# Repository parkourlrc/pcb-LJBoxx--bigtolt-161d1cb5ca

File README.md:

# BigTOLT - Big(kinda) esc with TOLT mosfets

18 mosfet TOLT package esc design based off vesc6 schematic and compatible with [VESC](https://github.com/vedderb/bldc) firmware.

There is also a small high voltage converter used for higher voltage operation, aim was to have a quite big voltage operation range. But if you will test it with high voltage, please do mind that the voltage sensing is **un-isolated**

# Tested !!
This board is tested but the pcb needs some fixes (will do soon). BOM and gerber are in [here](/tolt)

## Board preview

## Liability
This project sources are provided **as is** therfore I, and the co controbutors to this repository shall not be held responsible for any damage occured, including but not limited to hardware damages or other physical injury caused by the outcomes of this source. **You are responsible for your actions. If used wrong, it will go wrong!**

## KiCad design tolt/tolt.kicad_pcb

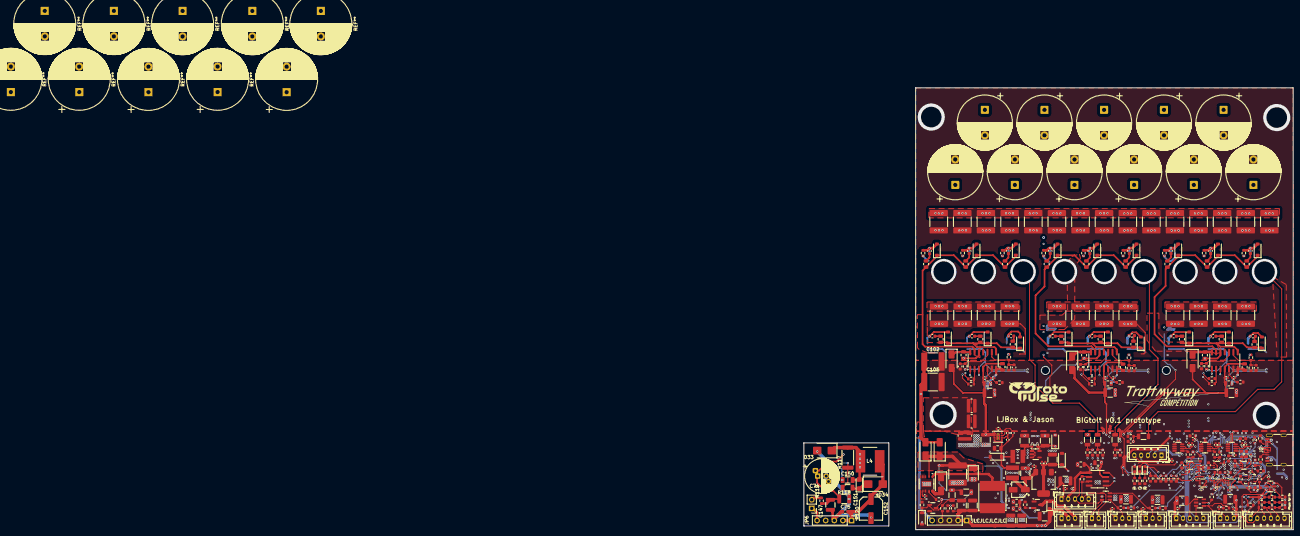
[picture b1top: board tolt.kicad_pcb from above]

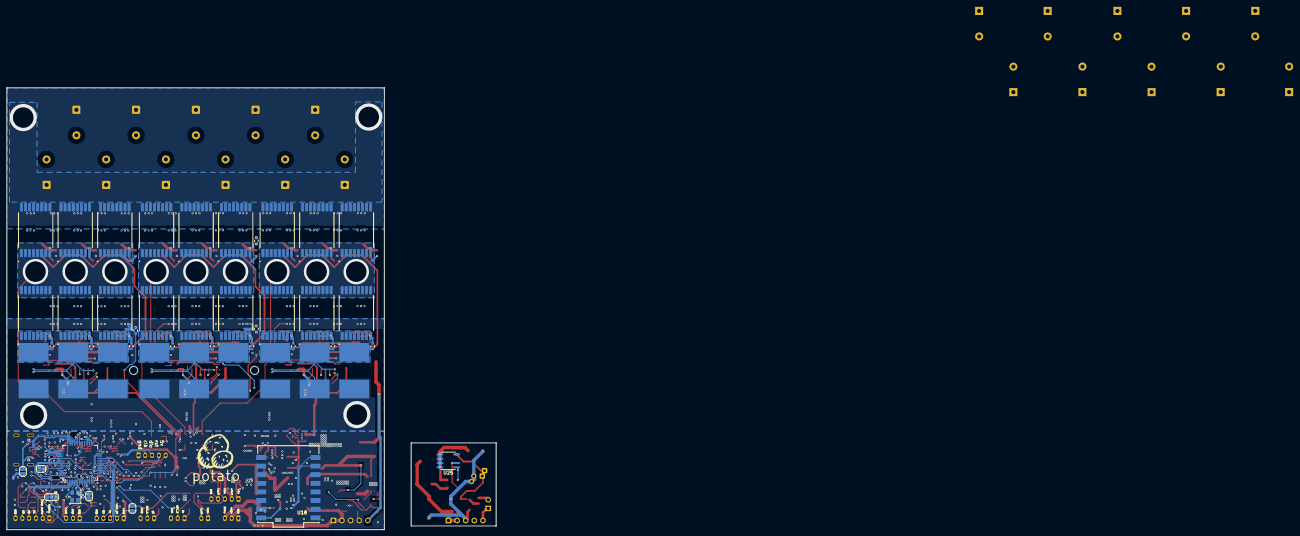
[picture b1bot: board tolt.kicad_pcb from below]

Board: 6 copper layers, 111.1 x 130.0 mm, 398 parts (50 on the bottom side), 164 nets.

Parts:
C1, C2, C3, C4, C24, C25, C26, C27, C28, C31, C32, C33, C34, C37, C38, C39, C45, C46, C47, C48, C49, C50, C76, C79, C80, C82, C87, C144: 100n; C_0402_1005Metric
C5, C6, C7, C8, C9, C10, C13, C14, C58, C59, C60, C78: 2.2uf; C_0603_1608Metric
C11, C12: 15p; C_0402_1005Metric
C15, C17, C19, C21, C22, C23, C81, C83, C84, C91, C111, C145, C146: 4.7u; C_0805_2012Metric
C16, C18, C20: 220nF; C_0402_1005Metric
C29, C36, C41: 15n; C_0603_1608Metric
C30, C35, C40, C51, C52, C53, C153, C154, C155: 1n; C_0603_1608Metric
C42, C43, C44, C71, C85, C88, C149: 10uF; C_1210_3225Metric
C54, C55, C56, C57: 100n; C_0603_1608Metric
C61: 33uF; CP_Elec_4x5.4
C62, C64, C67, C69, C116, C118, C120, C122, C123, C125, C127: 100nF; C_0402_1005Metric
C63, C65, C68, C70, C117, C119, C121, C124, C126: 2.2uF; C_1210_3225Metric
C66: 100uF; C_0402_1005Metric
C72: 430pF; R_0402_1005Metric
C73: 47uF; C_0805_2012Metric
C74: 33uF; CP_Radial_D10.0mm_P2.50mm_P5.00mm
C75: 470nF; C_1210_3225Metric
C77, C148: 22uF; C_1210_3225Metric
C86: 33uF; CP_EIA-3528-15_AVX-H
C89, C90, C92, C93, C94, C95, C96, C97, C98, C99, C100: 560u; CP_Radial_D16.0mm_P7.50mm
C101, C102, C103, C104, C105, C106, C107, C108, C109, C110, C112, C113, C114, C115, C128, C129, C130, C131, C132, C133, C134, C135, C136, C137, C138, C139, C140, C141, C142, C143: 1uf; C_2220_5750Metric
C147: 100n; C_1210_3225Metric
C150: 100nF; C_1206_3216Metric
C151: 10uF; CP_EIA-3216-18_Kemet-A
C152: 100uF; CP_Elec_6.3x5.4
D1, D2, D3: STTH2R06A; D_SMA
D4, D5, D6, D7, D8, D9, D10, D11, D12, D13, D14, D15, D16, D17, D18, D19, D20, D21: D; D_SOD-123
D22: green; LED_0603_1608Metric
D23: MMSZ5242B; D_SOD-123
D24, D25: BZT52C3V6-7-F; D_SOD-123
D26: red; LED_0603_1608Metric
D27: blue; LED_0603_1608Metric
D28: BAT46W; D_SOD-323F
D29: BZT52C5V6-7-F; D_SOD-123
D30, D31, D32: SS1200; D_SMA
D33, D34: STTH1R06U; D_SMB
FB1, FB2, FB3, FB4, FB5, FB6, FB7, FB8, FB9, FB10, FB11, FB12, FB13, FB14, FB15, FB16, FB17, FB18: FerriteBead; C_0603_1608Metric
J1, J4, J7: Conn_01x05; JST_PH_B5B-PH-K_1x05_P2.00mm_Vertical
J2: USB_C_Receptacle_USB2.0; USB_C_Receptacle_G-Switch_GT-USB-7010ASV
J3: Conn_01x06; JST_PH_B6B-PH-K_1x06_P2.00mm_Vertical
J5, J6, J9, J10: Conn_01x03; JST_PH_B3B-PH-K_1x03_P2.00mm_Vertical
J8: Conn_01x02; JST_PH_B2B-PH-K_1x02_P2.00mm_Vertical
J11, J11#2: Conn_01x05; PinHeader_1x05_P2.54mm_Vertical
J14: BOOT0; SolderJumper-2_P1.3mm_Open_RoundedPad1.0x1.5mm
J15: NRST; SolderJumper-2_P1.3mm_Open_RoundedPad1.0x1.5mm
JP1: Jumper_3_Bridged12; SolderJumper-3_P1.3mm_Bridged2Bar12_RoundedPad1.0x1.5mm
JP2, JP3: Jumper_2_Open; SolderJumper-2_P1.3mm_Open_RoundedPad1.0x1.5mm
JP6: Jumper_2_Open; PinHeader_1x02_P2.54mm_Vertical
L1, L2: 10uh; IND-SMD_L3.9-W3.9-1
L4: 1.5mH; L_Bourns_SRN8040TA
L5: 220uH; IND-SMD_L8.0-W8.0_FNR80XXS
Q1, Q2, Q3, Q4, Q5, Q6, Q7, Q8, Q9, Q10, Q11, Q12, Q13, Q14, Q15, Q16, Q17, Q18: NMOS; HDSOP-16-2
Q19: CJ3400; SOT-23
Q20: BSS131; SOT-23
R1, R2, R3, R37, R38, R39, R40, R41, R42, R52, R54, R55, R56, R57, R61, R62, R63, R72, R85, R86, R87, R88, R89, R90, R91, R92, R93, R99, R103, R104, R105, R106, R107, R108, R109, R110, R111, R121: 10k; R_0603_1608Metric
R4, R68, R69: 0; R_0815_2038Metric
R5, R6, R7, R8, R9, R10, R14, R15, R16, R17, R18, R19, R23, R24, R25, R27, R28, R29: 24r; R_0805_2012Metric
R11, R12, R13, R20, R21, R22, R30, R31, R32: 0.3mr; R5930
R26, R84: 5k1; R_0603_1608Metric
R33, R34, R35, R67, R70, R71, R115: 1k; R_0603_1608Metric
R36, R51, R53: 320k; R_0603_1608Metric
R43, R45, R47: 240k; R_1206_3216Metric
R44, R46, R48: 5.1k; R_0603_1608Metric
R49, R96: 470k; R_1206_3216Metric
R50: 10.2k; R_0603_1608Metric
R58, R59, R60: 10k_NTC; R_0603_1608Metric_Pad0.98x0.95mm_HandSolder
R64: 523k; R_0402_1005Metric
R65, R66: 220r; R_0603_1608Metric
R73, R74, R75, R79, R81, R100, R101, R102: 2k2; R_0603_1608Metric
R76, R77, R78, R80, R82: 4.3k; R_0603_1608Metric
R83: 120ohm; R_0603_1608Metric
R94, R95: 100k; R_0402_1005Metric
R97: 470r; R_0603_1608Metric
R98, R122, R123, R124: 100r; R_0603_1608Metric
R112: 2.8M; R_0603_1608Metric
R113: 200k; R_0603_1608Metric
R114: 4.7M; R_1206_3216Metric
R116: 100k; R_0603_1608Metric
R117: 2k; R_2512_6332Metric
R118: 12.7k; R_1206_3216Metric
R119: 0; R_0603_1608Metric
R120: 4k; R_0603_1608Metric
U1: STM32F405RGTx; LQFP-64_10x10mm_P0.5mm
U2, U3, U4: L6491; SO-14_3.9x8.65mm_P1.27mm
U5, U7, U9: INA240/241; SOT-23-8
U6, U8, U10, U11, U12, U13: MC74VHC1GT66; SOT-353_SC-70-5
U14: AMS1117-3.3; SOT-223-3_TabPin2
U15: LP5907MFX-3.3; SOT-23-5
U16: TPS82130; Texas_SIL0008D_MicroSiP-8-1EP_2.8x3mm_P0.65mm_EP1.1x1.9mm_T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
U17: BMI323; Bosch_LGA-14_3x2.5mm_P0.5mm
U18: ESP32-C3_SUPERMINI_SMD; MODULE_ESP32-C3_SUPERMINI
U20: TJA1051T-3; SOIC-8_3.9x4.9mm_P1.27mm
U21, U22, U23: SRV05-4; SOT-23-6
U24: LTC7138xMSE; Analog_MSOP-12-16-1EP_3x4.039mm_P0.5mm_EP1.651x2.845mm
U25: LNK306D; PowerIntegrations_SO-8C
Y1: 8m; Crystal_SMD_3225-4Pin_3.2x2.5mm

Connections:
+5V: C73.2, C80.2, C83.2, C84.2, C91.2, C118.1, C119.1, C120.1, C121.1, C122.2, C125.1, C126.1, D29.1 (K), J1.5, J4.1, J5.1, J6.1, JP1.3 (B), JP3.2 (B), L1.1, L2.1, R64.1, R95.2, U16.4 (VOUT), U16.5 (VOUT), U18.5V, U20.3 (VCC), U22.5 (VP)
+12V: C21.2, C22.2, C23.2, C24.2, C25.2, C26.2, C42.1, C43.1, C44.1, C71.2, C77.2, C85.2, C88.2, C111.2, C145.2, C146.2, C148.2, C149.2, C152.1, D1.2 (A), D2.2 (A), D3.2 (A), D28.1 (K), D34.2 (A), J10.2, J11.1, J11.2, J11#2.1, J11#2.2, L4.2, L5.2, R112.1, R120.1, U2.4 (VCC), U3.4 (VCC), U4.4 (VCC), U16.1 (EN), U16.2 (VIN)
+BATT: C89.1, C90.1, C92.1, C93.1, C94.1, C95.1, C96.1, C97.1, C98.1, C99.1, C100.1, C101.1, C102.1, C103.1, C104.1, C105.1, C106.1, C107.1, C108.1, C109.1, C110.1, C112.1, C113.1, C114.1, C115.1, C128.1, C129.1, C130.1, C131.1, C132.1, C133.1, C134.1, C135.1, C136.1, C137.1, C138.1, C139.1, C140.1, C141.1, C142.1, D31.2 (A), D32.2 (A), J11.5, J11#2.5, JP6.1 (A), Q1.1 (D), Q2.1 (D), Q3.1 (D), Q7.1 (D), Q8.1 (D), Q9.1 (D), Q13.1 (D), Q14.1 (D), Q15.1 (D), R49.1
/INTER/BRK: R40.2, R41.1, R42.1, R121.1
/INTER/G_H_A: D7.1 (K), D8.1 (K), D9.1 (K), R5.1, R6.1, R7.2, U2.13 (HVG)
/INTER/G_H_B: D10.1 (K), D11.1 (K), D12.1 (K), R14.1, R15.1, R16.2, U3.13 (HVG)
/INTER/G_H_C: D16.1 (K), D17.1 (K), D18.1 (K), R23.1, R24.1, R25.2, U4.13 (HVG)
/INTER/G_L_A: D4.1 (K), D5.1 (K), D6.1 (K), R8.1, R9.1, R10.2, U2.8 (LVG)
/INTER/G_L_B: D13.1 (K), D14.1 (K), D15.1 (K), R17.1, R18.1, R19.2, U3.8 (LVG)
/INTER/G_L_C: D19.1 (K), D20.1 (K), D21.1 (K), R27.1, R28.1, R29.2, U4.8 (LVG)
/INTER/H_A: U1.41 (PA8), U2.3 (HIN)
/INTER/H_B: U1.42 (PA9), U3.3 (HIN)
/INTER/H_C: U1.43 (PA10), U4.3 (HIN)
/INTER/L_A: U1.34 (PB13), U2.1 (~LIN)
/INTER/L_B: U1.35 (PB14), U3.1 (~LIN)
/INTER/L_C: U1.36 (PB15), U4.1 (~LIN)
/INTER/Ph_a: C15.2, Q1.3 (S), Q2.3 (S), Q3.3 (S), Q4.1 (D), Q5.1 (D), Q6.1 (D), R43.1, R103.1, R104.2, R105.1, U2.12 (OUT)
/INTER/Ph_b: C17.2, Q7.3 (S), Q8.3 (S), Q9.3 (S), Q10.1 (D), Q11.1 (D), Q12.1 (D), R45.1, R106.1, R107.2, R108.1, U3.12 (OUT)
/INTER/Ph_c: C19.2, Q13.3 (S), Q14.3 (S), Q15.3 (S), Q16.1 (D), Q17.1 (D), Q18.1 (D), R47.1, R109.1, R110.2, R111.1, U4.12 (OUT)
/INTER/V1: C45.2, C54.1, R43.2, R44.1, U1.14 (PA0)
/INTER/V2: C46.2, C55.1, R45.2, R46.1, U1.15 (PA1)
/INTER/V3: C47.2, C57.1, R47.2, R48.1, U1.16 (PA2)
/INTER/V_supply: C56.1, R49.2, R50.1, U1.11 (PC3)
/IO/ADC_15: J7.2, JP2.2 (B), U1.25 (PC5)
/IO/CAN_RX: U1.61 (PB8), U20.4 (RXD)
/IO/CAN_TX: U1.62 (PB9), U20.1 (TXD)
/IO/HALL_1: R78.2, R102.1, U1.4 (PC15), U21.1 (IO1)
/IO/HALL_2: R77.2, R101.1, U1.3 (PC14), U21.3 (IO2)
/IO/HALL_3: R76.2, R100.1, U1.2 (PC13), U21.4 (IO3)
/IO/MISO_ADC_EXT2: R81.1, R82.2, U1.22 (PA6)
/IO/RX_SDA_NSS: J7.4, U1.20 (PA4), U1.30 (PB11), U23.3 (IO2)
/IO/SCK_ADC_EXT: JP2.1 (A), R79.1, R80.2, U1.21 (PA5)
/IO/SERVO: C87.2, R98.1, U1.58 (PB6)
/IO/SWCLK: J1.2, U1.49 (PA14)
/IO/SWDIO: J1.3, U1.46 (PA13)
/IO/TEMP_MOTOR: J3.2, R72.1, U1.24 (PC4), U21.6 (IO4)
/IO/TX_SCL_MOSI: J7.3, U1.23 (PA7), U1.29 (PB10), U23.1 (IO1)
/IO/USBD+: J2.A6 (D+), J2.B6 (D+), U1.45 (PA12)
/IO/USBD-: J2.A7 (D-), J2.B7 (D-), U1.44 (PA11)
/IO/aux: Q19.2 (G), R99.2, U1.53 (PC12)
/IO/rst: J1.4, J15.2, R39.2, U1.7 (NRST)
/aux logic/PC10_UART_TX: U1.51 (PC10), U18.21 (GPIO21)
/aux logic/PC11_UART_RX: U1.52 (PC11), U18.20 (GPIO20)
/aux logic/scl_bmi: R71.2, U1.55 (PB3), U17.13 (SCx)
/aux logic/sda_bmi: R70.2, U1.56 (PB4), U17.14 (SDx)
/logic/ADC_T1: C58.1, R58.2, R61.1, U1.17 (PA3)
/logic/ADC_T2: C59.1, R59.2, R62.1, U1.26 (PB0)
/logic/ADC_T3: C60.1, R60.2, R63.1, U1.27 (PB1)
/logic/BRK: R121.2, U1.50 (PA15)
/logic/led_green: D22.2 (A), U1.57 (PB5)
/logic/led_red: D26.2 (A), U1.59 (PB7)
CURRENT_1: C40.1, R35.2, U1.8 (PC0), U8.1
CURRENT_2: C35.1, R34.2, U1.9 (PC1), U6.1
CURRENT_3: C30.1, R33.2, U1.10 (PC2), U10.1
CURRENT_FILTER: U1.54 (PD2), U6.4, U8.4, U10.4
Canh: J4.4, J8.2, R83.1, U20.7 (CANH), U22.4 (IO3)
Canl: J4.3, J8.1, R83.2, U20.6 (CANL), U22.6 (IO4)
GND: C1.1, C2.1, C3.1, C4.1, C5.1, C6.1, C7.1, C8.1, C9.1, C10.1, C11.2, C12.2, C13.1, C14.1, C16.1, C18.1, C20.1, C24.1, C25.1, C26.1, C27.1, C28.1, C29.2, C30.2, C31.1, C32.1, C33.1, C34.1, C35.2, C36.2, C37.1, C38.1, C39.1, C40.2, C41.2, C48.1, C49.1, C50.1, C51.2, C52.2, C53.2, C54.2, C55.2, C56.2, C57.2, C58.2, C59.2, C60.2, C61.2, C62.2, C63.2, C64.2, C65.2, C66.2, C67.2, C68.2, C69.2, C70.2, C71.1, C72.2, C73.1, C74.2, C75.2, C76.1, C77.1, C78.1, C79.1, C80.1, C81.1, C82.1, C83.1, C84.1, C85.1, C86.2, C87.1, C88.1, C91.1, C102.2, C105.2, C116.2, C117.2, C118.2, C119.2, C120.2, C121.2, C122.1, C123.2, C124.2, C125.2, C126.2, C127.2, C143.2, C144.1, C147.2, C148.1, C149.1, C152.2, C153.2, C154.2, C155.2, D23.2 (A), D24.2 (A), D25.2 (A), D29.2 (A), D33.2 (A), J1.1, J2.A1 (GND), J2.A12 (GND), J2.B1 (GND), J2.B12 (GND), J2.S1 (SHIELD), J3.6, J4.5, J5.3, J6.3, J7.5, J9.1, J10.1, J11.3, J11#2.3, J15.1, Q19.1 (D), Q20.2 (S), R1.2, R2.2, R3.2, R4.2, R26.1, R37.2, R38.2, R44.2, R46.2, R48.2, R50.2, R52.2, R54.2, R61.2, R62.2, R63.2, R65.1, R66.1, R67.1, R68.1, R69.1, R76.1, R77.1, R78.1, R80.1, R82.1, R84.1, R94.2, R99.1, R113.2, R116.1, R120.2, U1.12 (VSSA), U1.18 (VSS), U1.63 (VSS), U2.6 (SGND), U3.6 (SGND), U4.6 (SGND), U5.2 (GND), U5.3 (REF2), U6.3 (GND), U7.2 (GND), U7.3 (REF2), U8.3 (GND), U9.2 (GND), U9.3 (REF2), U10.3 (GND), U11.2, U11.3 (GND), U12.2, U12.3 (GND), U13.2, U13.3 (GND), U14.1 (GND), U15.2 (GND), U16.3 (GND), U16.9 (GND), U17.6 (GNDIO), U17.7 (GND), U18.G (GND), U20.2 (GND), U20.8 (S), U21.2 (VN), U22.2 (VN), U23.2 (VN), U24.6 (VPRG2), U24.7 (VPRG1), U24.8 (GND), U24.12 (OVLO), U24.17 (GND), Y1.2, Y1.4
GNDPWR: C21.1, C22.1, C23.1, C42.2, C43.2, C44.2, C89.2, C90.2, C92.2, C93.2, C94.2, C95.2, C96.2, C97.2, C98.2, C99.2, C100.2, C101.2, C103.2, C104.2, C106.2, C107.2, C108.2, C109.2, C110.2, C111.1, C112.2, C113.2, C114.2, C115.2, C128.2, C129.2, C130.2, C131.2, C132.2, C133.2, C134.2, C135.2, C136.2, C137.2, C138.2, C139.2, C140.2, C141.2, C142.2, C145.1, C146.1, R4.1, R11.2, R12.2, R13.2, R20.2, R21.2, R22.2, R30.2, R31.2, R32.2, R68.2, R69.2, U2.7 (PGND), U3.7 (PGND), U4.7 (PGND)
unnamed: C29.1, U10.2
unnamed: C36.1, U6.2
unnamed: C41.1, U8.2
unnamed: C45.1, U11.1
unnamed: C46.1, U12.1
unnamed: C47.1, U13.1
unnamed: C15.1, D1.1 (K), U2.14 (BOOT)
unnamed: C17.1, D2.1 (K), U3.14 (BOOT)
unnamed: C19.1, D3.1 (K), U4.14 (BOOT)
unnamed: D4.2 (A), FB18.2, Q6.2 (G), R87.2
unnamed: D5.2 (A), FB17.2, Q5.2 (G), R86.2
unnamed: D6.2 (A), FB16.2, Q4.2 (G), R85.2
unnamed: D7.2 (A), FB15.2, Q3.2 (G), R105.2
unnamed: D8.2 (A), FB14.2, Q2.2 (G), R104.1
unnamed: D9.2 (A), FB13.2, Q1.2 (G), R103.2
unnamed: D10.2 (A), FB11.2, Q9.2 (G), R108.2
unnamed: D11.2 (A), FB9.2, Q8.2 (G), R107.1
unnamed: D12.2 (A), FB7.2, Q7.2 (G), R106.2
unnamed: D13.2 (A), FB12.2, Q12.2 (G), R90.2
unnamed: D14.2 (A), FB10.2, Q11.2 (G), R89.2
unnamed: D15.2 (A), FB8.2, Q10.2 (G), R88.2
unnamed: D16.2 (A), FB1.2, Q15.2 (G), R111.2
unnamed: D17.2 (A), FB3.2, Q14.2 (G), R110.1
unnamed: D18.2 (A), FB5.2, Q13.2 (G), R109.2
unnamed: D19.2 (A), FB2.2, Q18.2 (G), R93.2
unnamed: D20.2 (A), FB4.2, Q17.2 (G), R92.2
unnamed: D21.2 (A), FB6.2, Q16.2 (G), R91.2
unnamed: D22.1 (K), R65.2
unnamed: D23.1 (K), Q20.1 (G), R96.1, R97.2, R116.2
unnamed: D26.1 (K), R66.2
unnamed: D27.1 (K), R67.2
unnamed: D28.2 (A), J10.3, Q19.3 (S)
unnamed: D30.2 (A), U24.16 (ANODE)
unnamed: D30.1 (K), L5.1, U24.1 (SW)
unnamed: C86.1, C143.1, D31.1 (K), D32.1 (K), R96.2, R114.1, U24.3 (VIN)
unnamed: C150.2, C151.2, D33.1 (K), L4.1, R117.2, U25.5 (S), U25.6 (S), U25.7 (S), U25.8 (S)
unnamed: C151.1, D34.1 (K), R118.2
unnamed: FB1.1, R23.2
unnamed: FB2.1, R27.2
unnamed: FB3.1, R24.2
unnamed: FB4.1, R28.2
unnamed: FB5.1, R25.1
unnamed: FB6.1, R29.1
unnamed: FB7.1, R16.1
unnamed: FB8.1, R19.1
unnamed: FB9.1, R15.2
unnamed: FB10.1, R18.2
unnamed: FB11.1, R14.2
unnamed: FB12.1, R17.2
unnamed: FB13.1, R7.1
unnamed: FB14.1, R6.2
unnamed: FB15.1, R5.2
unnamed: FB16.1, R10.1
unnamed: FB17.1, R9.2
unnamed: FB18.1, R8.2
unnamed: J2.A5 (CC1), R26.2
unnamed: J2.B5 (CC2), R84.2
unnamed: J3.1, JP1.2 (C), R73.2, R74.2, R75.2, U21.5 (VP)
unnamed: J3.3, R73.1, R102.2
unnamed: J3.4, R74.1, R101.2
unnamed: J3.5, R75.1, R100.2
unnamed: J14.2, R38.1, U1.60 (BOOT0)
unnamed: J2.A4 (VBUS), J2.A9 (VBUS), J2.B4 (VBUS), J2.B9 (VBUS), JP3.1 (A)
unnamed: JP6.2 (B), R119.1
unnamed: Q20.3 (D), R114.2, R115.1
unnamed: C11.1, U1.5 (PH0), Y1.3
unnamed: C12.1, U1.6 (PH1), Y1.1
unnamed: C13.2, U1.31 (VCAP_1)
unnamed: C14.2, U1.47 (VCAP_2)
unnamed: C155.1, R124.2, U2.10 (CP+)
unnamed: C51.1, R36.2, R37.1, U2.9 (CP-)
unnamed: C16.2, R1.1, U2.5 (DT)
unnamed: R40.1, R55.2, U2.2 (~SD/OD)
unnamed: C154.1, R123.2, U3.10 (CP+)
unnamed: C52.1, R51.2, R52.1, U3.9 (CP-)
unnamed: C18.2, R2.1, U3.5 (DT)
unnamed: R41.2, R56.2, U3.2 (~SD/OD)
unnamed: C153.1, R122.2, U4.10 (CP+)
unnamed: C53.1, R53.2, R54.1, U4.9 (CP-)
unnamed: C20.2, R3.1, U4.5 (DT)
unnamed: R42.2, R57.2, U4.2 (~SD/OD)
unnamed: R33.1, U5.5 (OUT)
unnamed: R34.1, U7.5 (OUT)
unnamed: R35.1, U9.5 (OUT)
unnamed: C61.1, C62.1, C63.1, L1.2, U14.3 (VI)
unnamed: C69.1, C70.1, L2.2, U15.1 (IN), U15.3 (EN)
unnamed: R64.2, R94.1, U16.6 (FB)
unnamed: R95.1, U16.7 (PG)
unnamed: C72.1, U16.8 (SS/TR)
unnamed: R115.2, U24.14 (RUN)
unnamed: C76.2, U24.10 (SS)
unnamed: R112.2, R113.1, U24.9 (VFB)
unnamed: C150.1, U25.1 (BP)
unnamed: C74.1, C75.1, C147.1, R119.2, U25.4 (D)
unnamed: R117.1, R118.1, U25.2 (FB)
SENS_A_P: Q4.3 (S), Q5.3 (S), Q6.3 (S), R11.1, R12.1, R13.1, R85.1, R86.1, R87.1, R124.1, U9.8 (IN+)
SENS_B_P: Q10.3 (S), Q11.3 (S), Q12.3 (S), R20.1, R21.1, R22.1, R88.1, R89.1, R90.1, R123.1, U7.8 (IN+)
SENS_C_P: Q16.3 (S), Q17.3 (S), Q18.3 (S), R30.1, R31.1, R32.1, R91.1, R92.1, R93.1, R122.1, U5.8 (IN+)
VCC: C1.2, C2.2, C3.2, C4.2, C5.2, C6.2, C7.2, C8.2, C64.1, C65.1, C66.1, C78.2, C79.2, C81.2, C82.2, C116.1, C117.1, C123.1, C124.1, C127.1, D24.1 (K), D27.2 (A), J4.2, J7.1, J9.3, J14.1, JP1.1 (A), R36.1, R39.1, R51.1, R53.1, R55.1, R56.1, R57.1, R58.1, R59.1, R60.1, R70.1, R71.1, R72.2, U1.1 (VBAT), U1.19 (VDD), U1.32 (VDD), U1.48 (VDD), U1.64 (VDD), U14.2 (VO), U17.5 (VDDIO), U20.5 (VIO), U23.5 (VP)
VDDA: C9.2, C10.2, C27.2, C28.2, C31.2, C32.2, C33.2, C34.2, C37.2, C38.2, C39.2, C48.2, C49.2, C50.2, C67.1, C68.1, C144.2, D25.1 (K), U1.13 (VDDA), U5.6 (Vs), U5.7 (REF1), U6.5 (V+), U7.6 (Vs), U7.7 (REF1), U8.5 (V+), U9.6 (Vs), U9.7 (REF1), U10.5 (V+), U11.5 (V+), U12.5 (V+), U13.5 (V+), U15.5 (OUT), U17.8 (VDD)
Vreg_en: J11.4, J11#2.4, R97.1
adc1: J5.2, R79.2, U22.3 (IO2)
adc2: J6.2, R81.2, U22.1 (IO1)
ph_filt: U1.40 (PC9), U11.4, U12.4, U13.4
ppm: J9.2, R98.2, U23.4 (IO3)

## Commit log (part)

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2026-05-21 prod
